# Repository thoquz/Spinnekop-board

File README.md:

# Spinnekop-board
### A minimalist development board for 8-pin ATtiny series chips from Atmel.
---

Basic useful feature list:

 * Designed to be put on the edge of a breadboard, thus taking up minimal space for prototyping.
 * Acts as a breakout board for surface-mount ATtiny chips, each pin is directly broken out the same as the chip's topology.
 * Can be easily made at home, only a single layer of copper traces and 8 components. (including connectors)
 * Supports the ATtiny13/45/85 chips.
 * A programming port. (6-pin ICSP)
 * A linear voltage regulator for powering the board externally. (The LM78L05 can be swapped with a LP2950)

The board is designed in [KiCAD](www.kicad-pcb.org)

The [example code](https://github.com/thoquz/Spinnekop-board/blob/master/example%20code/examplePWM.c) requires the [avr-gcc compiler](https://gcc.gnu.org/wiki/avr-gcc).

Compiling and flashing the code on a Debian-based distro:

```Shell
sudo apt-get install gcc-avr binutils-avr gdb-avr avr-libc avrdude
make
make flash
```
If the last command fails, change the PROGRAMMER variable in the Makefile to match your programming device.
Consult the avrdude man page for the name of your programming device.

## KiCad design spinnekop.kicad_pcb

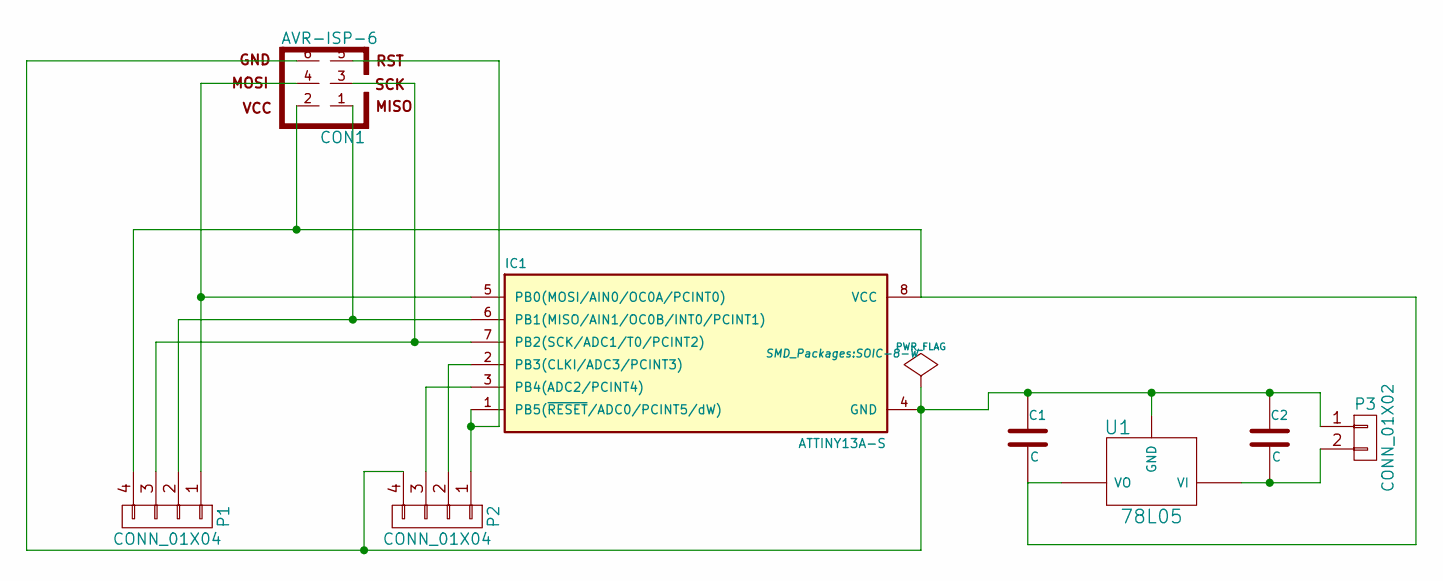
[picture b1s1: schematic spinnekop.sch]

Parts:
C1, C2: C; Capacitor3MMDiscRM2.5
CON1: AVR-ISP-6; Pin_Header_Straight_2x03
IC1: ATTINY13A-S; SOIC-8-W
P1, P2: CONN_01X04; Pin_Header_Straight_1x04
P3: CONN_01X02; Pin_Header_Straight_2x01
U1: 78L05; LM78LXX

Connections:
unnamed: C1.1, C2.1, CON1.6, IC1.4 (GND), P2.4, P3.1, U1.GND
unnamed: C1.2, CON1.2, IC1.8 (VCC), P1.4, U1.VO
unnamed: C2.2, P3.2, U1.VI
unnamed: CON1.1, IC1.6 (PB1(MISO/AIN1/OC0B/INT0/PCINT1)), P1.2
unnamed: CON1.3, IC1.7 (PB2(SCK/ADC1/T0/PCINT2)), P1.3
unnamed: CON1.4, IC1.5 (PB0(MOSI/AIN0/OC0A/PCINT0)), P1.1
unnamed: CON1.5, IC1.1 (PB5(~RESET~/ADC0/PCINT5/dW)), P2.1
unnamed: IC1.2 (PB3(CLKI/ADC3/PCINT3)), P2.2
unnamed: IC1.3 (PB4(ADC2/PCINT4)), P2.3

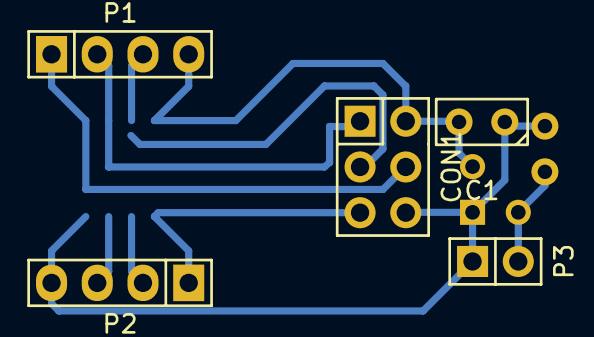
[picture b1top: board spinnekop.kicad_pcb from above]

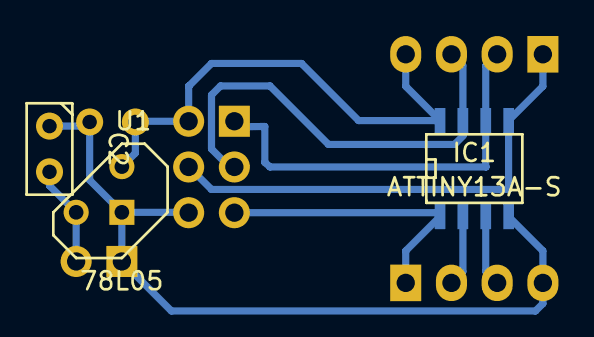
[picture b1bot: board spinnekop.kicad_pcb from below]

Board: 2 copper layers, 8 parts (3 on the bottom side), 9 nets.

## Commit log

2015-06-29 Documented the code example
2015-06-29 Made the README
    Documented the project
2015-06-29 Minor change of formatting
    Allows the commands to easily be copy and pasted instead.
2015-06-29 Linked to example code
